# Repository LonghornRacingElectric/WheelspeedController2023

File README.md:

# WheelspeedController
See Name

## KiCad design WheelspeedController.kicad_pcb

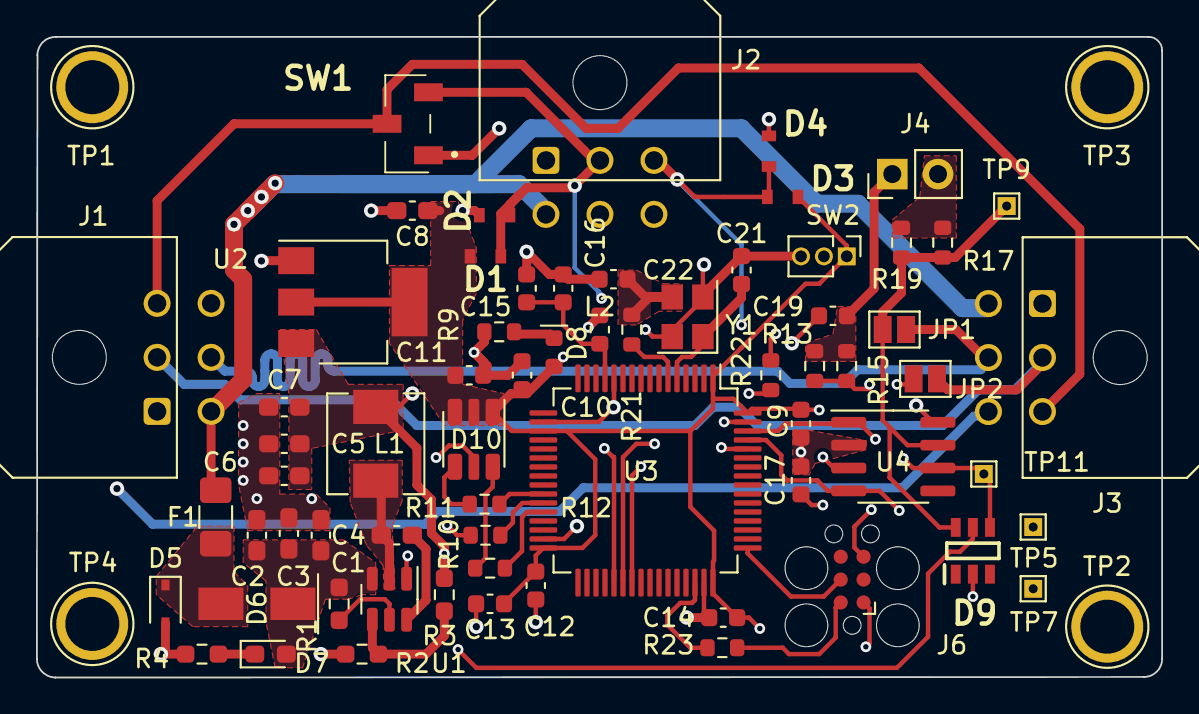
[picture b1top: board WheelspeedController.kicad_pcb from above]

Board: 4 copper layers, 62.5 x 35.6 mm, 70 parts (0 on the bottom side), 40 nets.

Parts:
C1, C2: 10uF; C_0603_1608Metric_Pad1.08x0.95mm_HandSolder
C3, C4: 100nF; C_0603_1608Metric_Pad1.08x0.95mm_HandSolder
C5, C6, C8: 22uF; C_0603_1608Metric_Pad1.08x0.95mm_HandSolder
C7: 1uF; C_0603_1608Metric_Pad1.08x0.95mm_HandSolder
C9: 4u7; C_0603_1608Metric
C10, C11, C12, C13, C14: 100n; C_0603_1608Metric
C15: 1u; C_0603_1608Metric
C16: 10n; C_0603_1608Metric
C17: 0u1; C_0603_1608Metric
C19: 4.7n; C_0603_1608Metric
C21, C22: 10p; C_0603_1608Metric
D1, D2, D3, D4: SD0603S040S0R2; SD0603
D5: 32V; D_SOD-323
D6: 0.7dV; D_SMA
D7: LED; LED_0603_1608Metric_Pad1.05x0.95mm_HandSolder
D8: RED; LED_0603_1608Metric
D9: DT1446-04TS-7; SOT95P280X100-6N
D10: SMLVN6RGB; LED_ROHM_SMLVN6
F1: 2A; Fuse_1206_3216Metric_Pad1.42x1.75mm_HandSolder
J1: DEUTSCH DT Inp; Molex_Micro-Fit_3.0_43045-0600_2x03_P3.00mm_Horizontal
J2: DEUTSCH DT Data; Molex_Micro-Fit_3.0_43045-0600_2x03_P3.00mm_Horizontal
J3: DEUTSCH DT Out; Molex_Micro-Fit_3.0_43045-0600_2x03_P3.00mm_Horizontal
J4: Conn_01x02; PinHeader_1x02_P2.54mm_Vertical
J6: SWD; Tag-Connect_TC2030-IDC-FP_2x03_P1.27mm_Vertical
JP1, JP2: SolderJumper-2_P1.3mm_Bridged2Bar_Pad1.0x1.5mm
L1: 4u7; L_Sunlord_MWSA0518_5.4x5.2mm
L2: 68n; L_0603_1608Metric
R1, R2: 10K; R_0603_1608Metric_Pad0.98x0.95mm_HandSolder
R3: 54.9K; R_0603_1608Metric_Pad0.98x0.95mm_HandSolder
R4: 470R; R_0603_1608Metric_Pad0.98x0.95mm_HandSolder
R9: 100; R_0603_1608Metric
R10, R11, R12: 220; R_0603_1608Metric
R13, R15, R17, R19: 120; R_0603_1608Metric
R21: 47; R_0603_1608Metric
R22: 10K; R_0603_1608Metric
R23: 22; R_0603_1608Metric
SW1: SW_SPDT; CAS120A1
SW2: SW_SPDT; PinHeader_1x03_P1.27mm_Vertical
TP1, TP2, TP3, TP4: TestPoint; TestPoint_Plated_Hole_D3.0mm
TP5, TP7, TP9, TP11: TestPoint_THTPad_1.0x1.0mm_Drill0.5mm
U1: LMR51420; SOT-23-6
U2: AMS1117-3.3; SOT-223-3_TabPin2
U3: STM32F105RCTx; LQFP-64_10x10mm_P0.5mm
U4: SN65HVD230; SOIC-8_3.9x4.9mm_P1.27mm
Y1: 16MHz; Crystal_SMD_3225-4Pin_3.2x2.5mm

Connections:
+3.3VA: C15.1, C16.1, L2.2, U3.13 (VDDA)
+3V3: C8.1, C9.1, C10.1, C11.1, C12.1, C13.1, C14.1, C17.1, D1.1, D3.1, D8.2 (A), D10.1 (BA), D10.2 (RA), D10.3 (GA), J6.1, L2.1, SW2.1 (A), U2.2 (VO), U3.1 (VBAT), U3.19 (VDD), U3.32 (VDD), U3.48 (VDD), U3.64 (VDD), U4.3 (VCC)
+5V: C5.1, C6.1, C7.1, D9.5 (VCC), J2.5, L1.2, R3.2, U2.3 (VI)
+24V: F1.2, J1.4, J2.4, J3.4
/CAN+: J1.5, J3.5, JP1.2 (B)
/CAN-: J1.2, J3.2, JP2.2 (B)
/Extra1: J2.6, U3.39 (PC8)
/MCU/BOOT0: R22.2, U3.60 (BOOT0)
/MCU/CAN1_RX: TP7.1, U3.61 (PB8), U4.4 (R)
/MCU/CAN1_TX: TP5.1, U3.62 (PB9), U4.1 (D)
/MCU/HSE_in: C21.1, U3.5 (PD0), Y1.1
/MCU/HSE_out: R21.1, U3.6 (PD1)
/MCU/LED_B: R10.2, U3.28 (PB2)
/MCU/LED_G: R11.2, U3.27 (PB1)
/MCU/LED_R: R12.2, U3.26 (PB0)
/MCU/SWCLK: J6.4, U3.49 (PA14)
/MCU/SWDIO: R23.2, U3.46 (PA13)
/PassThru: J1.3, J3.3, SW1.2 (B)
/SHIELD: J1.6, J3.6
/VRM/BUCK/EN: R1.2, U1.5 (EN)
/VRM/BUCK/SW: C4.1, L1.1, U1.2 (SW)
/VRM/BUCK/VBST: C4.2, U1.6 (VBST)
/VRM/BUCK/VFB: R2.1, R3.1, U1.4 (VFB)
/VRM/BUCK/V_in: C1.1, C2.1, C3.1, D6.1 (K), D7.2 (A), R1.1, U1.3 (VIN)
/VRM/DIODE: D5.1 (K), D6.2 (A), F1.1
/WheelIn1: D3.2, D4.1, J2.3, SW1.1 (A), U3.38 (PC7)
/WheelIn2: D1.2, D2.1, J2.2, SW1.3 (C), U3.37 (PC6)
GND: C1.2, C2.2, C3.2, C5.2, C6.2, C7.2, C8.2, C9.2, C10.2, C11.2, C12.2, C13.2, C14.2, C15.2, C16.2, C17.2, C19.1, C21.2, C22.2, D2.2, D4.2, D5.2 (A), D9.2 (VSS), J1.1, J2.1, J3.1, J6.5, R2.2, R4.1, R9.2, SW2.3 (C), TP1.1, TP2.1, TP3.1, TP4.1, U1.1 (GND), U2.1 (GND), U3.12 (VSSA), U3.18 (VSS), U3.31 (VSS), U3.47 (VSS), U3.63 (VSS), U4.2 (GND), U4.8 (Rs), Y1.2, Y1.4
unnamed: C19.2, J4.1, R13.1, R15.1
unnamed: C22.1, R21.2, Y1.3
unnamed: D7.1 (K), R4.2
unnamed: D8.1 (K), R9.1
unnamed: D9.4 (I/O3), JP2.1 (A), R13.2, R15.2, TP11.1, U4.6 (CANL)
unnamed: D9.6 (I/O4), JP1.1 (A), R17.1, R19.1, TP9.1, U4.7 (CANH)
unnamed: D10.4 (GK), R12.1
unnamed: D10.5 (RK), R11.1
unnamed: D10.6 (BK), R10.1
unnamed: J4.2, R17.2, R19.2
unnamed: J6.2, R23.1
unnamed: R22.1, SW2.2 (B)

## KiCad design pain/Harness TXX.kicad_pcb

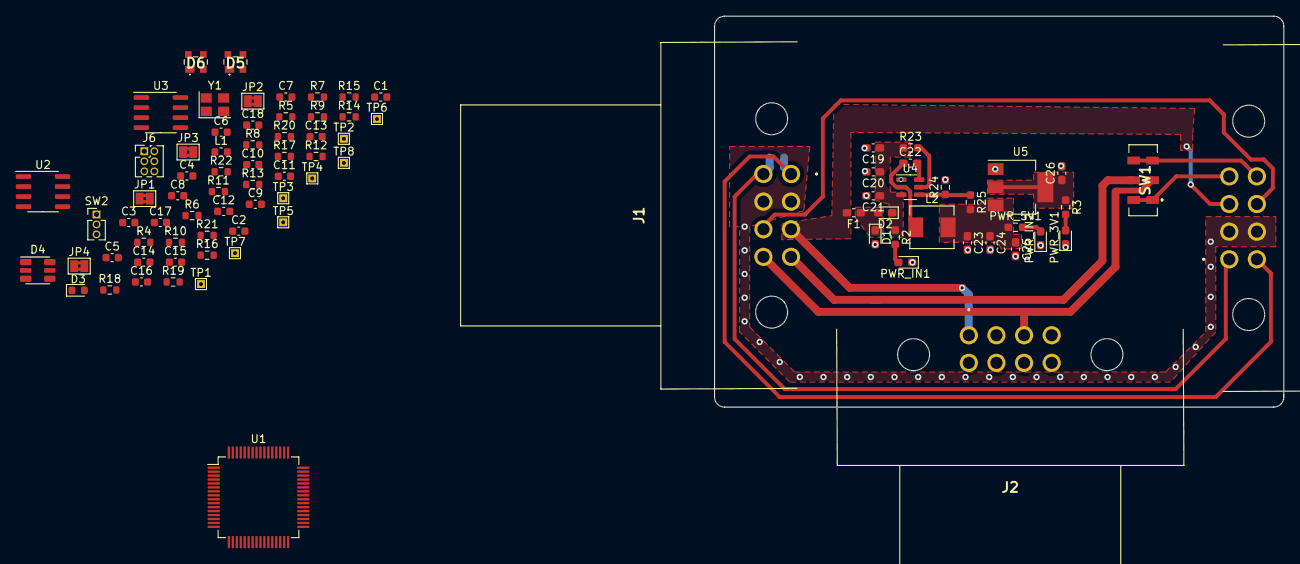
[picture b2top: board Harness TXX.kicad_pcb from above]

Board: 2 copper layers, 72.1 x 49.5 mm, 88 parts (1 on the bottom side), 54 nets.

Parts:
C1: 4u7; C_0603_1608Metric
C2, C3, C4, C5, C6: 100n; C_0603_1608Metric
C7: 1u; C_0603_1608Metric
C8: 10n; C_0603_1608Metric
C9, C10: 0u1; C_0603_1608Metric
C11, C12, C13, C14: 100p; C_0603_1608Metric
C15, C16: 4.7n; C_0603_1608Metric
C17, C18: 10p; C_0603_1608Metric
C19, C20: 10uF; C_0603_1608Metric_Pad1.08x0.95mm_HandSolder
C21, C22: 100nF; C_0603_1608Metric_Pad1.08x0.95mm_HandSolder
C23, C24, C26: 22uF; C_0603_1608Metric_Pad1.08x0.95mm_HandSolder
C25: 1uF; C_0603_1608Metric_Pad1.08x0.95mm_HandSolder
D1: 20V; D_0603_1608Metric_Pad1.05x0.95mm_HandSolder
D2: 0.7dV; D_0603_1608Metric_Pad1.05x0.95mm_HandSolder
D3: RED; LED_0603_1608Metric
D4: SMLVN6RGB; LED_ROHM_SMLVN6
D5, D6: CD143A-SR05; CD143ASR05
F1: 2A; Fuse_0603_1608Metric_Pad1.05x0.95mm_HandSolder
J1: InpConn; 348300801
J2: InSig; 348300801
J3: OutConn; 348300801
J6: SWD; PinHeader_2x03_P1.27mm_Vertical
JP1, JP2, JP3, JP4: SolderJumper-2_P1.3mm_Bridged2Bar_Pad1.0x1.5mm
L1: 68n; L_0603_1608Metric
L2: 4u7; L_Sunlord_MWSA0518_5.4x5.2mm
PWR_3V1: LED; LED_0603_1608Metric_Pad1.05x0.95mm_HandSolder
PWR_5V1: 100; R_0603_1608Metric_Pad0.98x0.95mm_HandSolder
PWR_IN1, PWR_IN2: LED; LED_0603_1608Metric_Pad1.05x0.95mm_HandSolder
R1: Rterm; R_0603_1608Metric_Pad0.98x0.95mm_HandSolder
R2: 470; R_0603_1608Metric_Pad0.98x0.95mm_HandSolder
R3: 0; R_0603_1608Metric_Pad0.98x0.95mm_HandSolder
R4, R5, R6, R7: 2k2; R_0603_1608Metric
R8: 100; R_0603_1608Metric
R9, R10, R11: 220; R_0603_1608Metric
R12, R13, R14, R15, R16, R17, R19, R20: 120; R_0603_1608Metric
R18: 47; R_0603_1608Metric
R21: 10K; R_0603_1608Metric
R22: 22; R_0603_1608Metric
R23, R24: 10K; R_0603_1608Metric_Pad0.98x0.95mm_HandSolder
R25: 54.9K; R_0603_1608Metric_Pad0.98x0.95mm_HandSolder
SW1: SW_DPDT; JS202011JCQN
SW2: SW_SPDT; PinHeader_1x03_P1.27mm_Vertical
TP1, TP2, TP3, TP4, TP5, TP6, TP7, TP8: TestPoint_THTPad_1.0x1.0mm_Drill0.5mm
U1: STM32F105RCTx; LQFP-64_10x10mm_P0.5mm
U2, U3: SN65HVD230; SOIC-8_3.9x4.9mm_P1.27mm
U4: TPS562200; SOT-23-6
U5: AMS1117-3.3; SOT-223-3_TabPin2
Y1: 16MHz; Crystal_SMD_3225-4Pin_3.2x2.5mm

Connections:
+3.3V: C1.1, C2.1, C3.1, C4.1, C5.1, C6.1, D3.2 (A), D4.1 (BA), D4.2 (RA), D4.3 (GA), J6.1, L1.1, R4.1, R5.1, R6.1, R7.1, SW2.1 (A), U1.1 (VBAT), U1.19 (VDD), U1.32 (VDD), U1.48 (VDD), U1.64 (VDD)
+3.3VA: C7.1, C8.1, L1.2, U1.13 (VDDA)
+3V3: C9.1, C10.1, U2.3 (VCC), U2.5 (Vref), U3.3 (VCC), U3.5 (Vref)
+12V: D5.4 (REF), D6.4 (REF), F1.2, J1.3, J2.1, J3.3
/3V3: C26.1, R3.1, U5.2 (VO)
/5V: C23.1, C24.1, C25.1, L2.2, PWR_5V1.1, R25.2, U5.3 (VI)
/CAN+: J1.5, J3.1, R1.2
/CAN-: J1.1, J3.5, R1.1
/ENCD1: J3.4, SW1.1 (A), SW1.7 (Passive)
/ENCD2: J3.8, SW1.3 (C), SW1.5 (Passive)
/MCU/BOOT0: R21.2, U1.60 (BOOT0)
/MCU/CAN1_RX: TP3.1, U1.61 (PB8), U2.4 (R)
/MCU/CAN1_TX: TP1.1, U1.62 (PB9), U2.1 (D)
/MCU/CAN2_RX: TP4.1, U1.33 (PB12), U3.4 (R)
/MCU/CAN2_TX: TP2.1, U1.34 (PB13), U3.1 (D)
/MCU/HSE_in: C17.1, U1.5 (PD0), Y1.1
/MCU/HSE_out: R18.1, U1.6 (PD1)
/MCU/I2C1_SCL: R4.2, U1.58 (PB6)
/MCU/I2C1_SDA: R5.2, U1.59 (PB7)
/MCU/I2C2_SCL: R6.2, U1.29 (PB10)
/MCU/I2C2_SDA: R7.2, U1.30 (PB11)
/MCU/LED_B: R9.2, U1.16 (PA2)
/MCU/LED_G: R10.2, U1.15 (PA1)
/MCU/LED_R: R11.2, U1.14 (PA0)
/MCU/SWCLK: J6.4, U1.49 (PA14)
/MCU/SWDIO: R22.2, U1.46 (PA13)
/MISC: J1.7, J3.7
/VRM/12V_Out_Protected: C19.1, C20.1, C21.1, D2.1 (K), R2.1, R23.1, U4.3 (VIN)
/VRM/BUCK/EN: R23.2, U4.5 (EN)
/VRM/BUCK/SW: C22.1, L2.1, U4.2 (SW)
/VRM/BUCK/VBST: C22.2, U4.6 (VBST)
/VRM/BUCK/VFB: R24.1, R25.1, U4.4 (VFB)
/WheelIn1: J1.4, SW1.6 (Passive)
/WheelIn2: J1.8, J2.3, SW1.2 (B)
GND: C1.2, C2.2, C3.2, C4.2, C5.2, C6.2, C7.2, C8.2, C9.2, C10.2, C11.2, C12.2, C13.2, C14.2, C15.1, C16.1, C17.2, C18.2, C19.2, C20.2, C21.2, C23.2, C24.2, C25.2, C26.2, D1.2 (A), D5.1 (GND), D6.1 (GND), J1.2, J1.6, J2.2, J3.2, J3.6, J6.5, PWR_3V1.1 (K), PWR_IN1.1 (K), PWR_IN2.1 (K), R8.2, R24.2, SW2.3 (C), U1.12 (VSSA), U1.18 (VSS), U1.31 (VSS), U1.47 (VSS), U1.63 (VSS), U2.2 (GND), U2.8 (Rs), U3.2 (GND), U3.8 (Rs), U4.1 (GND), U5.1 (GND), Y1.2, Y1.4
unnamed: C11.1, D5.2 (I/O_1), JP2.1 (A), R12.2, R14.2, TP7.1, U2.6 (CANL)
unnamed: C12.1, D6.2 (I/O_1), JP4.1 (A), R13.2, R15.2, TP8.1, U3.6 (CANL)
unnamed: C13.1, D5.3 (I/O_2), JP1.1 (A), R16.1, R19.1, TP5.1, U2.7 (CANH)
unnamed: C14.1, D6.3 (I/O_2), JP3.1 (A), R17.1, R20.1, TP6.1, U3.7 (CANH)
unnamed: C15.2, R12.1, R14.1
unnamed: C16.2, R13.1, R15.1
unnamed: C18.1, R18.2, Y1.3
unnamed: D1.1 (K), D2.2 (A), F1.1
unnamed: D3.1 (K), R8.1
unnamed: D4.4 (GK), R11.1
unnamed: D4.5 (RK), R10.1
unnamed: D4.6 (BK), R9.1
unnamed: R16.2, R19.2
unnamed: R17.2, R20.2
unnamed: J6.2, R22.1
unnamed: PWR_3V1.2 (A), R3.2
unnamed: PWR_5V1.2, PWR_IN2.2 (A)
unnamed: PWR_IN1.2 (A), R2.2
unnamed: R21.1, SW2.2 (B)

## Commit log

2022-11-06 plz wrk
2022-11-13 changed
2022-11-13 maybe
2022-11-13 I give up on life
2022-11-13 fixes
2022-11-13 made recommended adjustmetns
2022-11-13 del Kicadlib
2022-11-13 Updating lib
2022-11-13 Dakota's feedback
2022-11-27 Post Rylan Review Edits
2022-11-27 Workday progress
2022-11-27 resized board
2022-12-04 pwease work
2022-12-05 Workday 12/4/22
2022-12-17 Board wiring
2022-12-17 Had been modifying a file on my computer and not git on accident. Adding updated PCB to Git
2022-12-17 file renaming to make more sense
2022-12-17 fixed borders
2023-01-01 Updated to 4 layers. Bit late
2023-01-01 Aligned connectors
2023-01-01 gerbers
